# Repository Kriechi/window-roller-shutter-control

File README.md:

# Window Roller Shutter Control 3-gang with ESP8266

This project contains a 3-gang electric/motorized window roller shutter control
based on an ESP8266. The following resources are included:

* Full schematics and PCB designs
  * in KiCAD 5 with all footprints
  * generated Gerber files ready to send to PCB manufacturer
  * exported as PDF file
* Microcontroller ESP8266 firmware source code
  * with WiFi connectivity and remote over-the-air update
  * for control via MQTT and a web interface
* 3D-printable enclosure
  * in 3MF and STL file formats

## Hardware

This projects was designed to control 3 independent electric roller shutter
motors, each with a hot (live) and two switched directional wires (L1 for "up"
and L2 for "down"). Existing manual switches need to be removed and the motor
cables are wired to screw terminals on the PCB. Two relays per roller shutter
control the direction: up or down. The circuit and the relay type ensure that
only one direction is possible at a time. The relays open before closing
(break-before-make), and both relays are arranged "in series" to control the
motor direction.

The PCB and enclosure are designed to fit around an existing 3-gang 60mm switch
box. Any common 3-gang switch plate for this size can be replaced by the PCB and
enclosure, given that each switch box is 72mm apart from its neighbor switch
box. The enclosure mounts flush against the wall and is secured by multiple
screws into the switch box behind it.

Since not every roller shutter provides a neutral (return) wire, an external
5-24VDC power supply (wall plug) is used to power the ESP8266 and relays on PCB.
This securely separates low-voltage from high-voltage, also see separation slots
on the PCB. Multiple footprints are on the PCB to feed in DC low-voltage.

Momentary toggle switches can be added to manually control the roller shutters,
independent of the ESP8266 or automation. The enclosure is designed for 6mm
toggle switches. They control the relays low-voltage side and override signals
from the ESP8266.

### Bill of Material

For the PCB assembly:

* 1x NodeMCU module for ESP8266, or ESP-12E module (requires additional components)
* 3x HB-9500 3P screw terminal, 9.5mm pitch
* 6x SRD-05VDC-SL-C relay, 5VDC control, opening before closing, 10A@250VAC
* 6x NPN transistor, footprint SOT-23, 2N3904 or similar
* 6x 220 Ohm resistor, footprint 1206
* 6x flyback diode, footprint 1206, 1N4001 or similar
* 3x MTS-123 On-Off-On toggle switch
* 1x 5V DC-DC voltage regulator, footprint SOT-223-3, AMS1117-50 or similar
* 1x 3.3V DC-DC voltage regulator if ESP-12E is used, footprint SOT-223-3, AMS1117-33 or similar
* 1x suitable power supply for 5VDC, at least 10W
* optional: capacitors as needed per voltage rail

For the enclosure and mounting:

* 8x M3 nut
* 4x M3x12 bolts
* 2x 3.2mm switch box screws (optional, up to 6x)

### Wiring

Each roller shutter is controlled by two relays accessible via a 3-way screw
terminal block. The center connection is the hot / live wire. The outer
connections are the directional L1 and L2 wires. If you roller shutters is
moving in the wrong direction, e.g., up instead of down, simply reverse the
wires on the outer connections on the this screw terminal block.

The toggle switches are wired in a similar way: the center pin is the common
connection, and the two outer pins control the up or down signal to the ESP8266.

The ESP8266 ESP-12E module needs an external 3.3V regulator, while the NodeMCU
module has one built in and only needs a 5V input (see available footprints on
the PCB). Various footprints for decoupling capacitors are available and can be
populated.

## Firmware / Control Software

The ESP8266 microcontroller can be flashed with the provided PlatformIO-based
firmware project. It controls the following functions:

* WiFi connectivity
* MQTT connection
  * with status updates being published to `window_shutter_status` topic
  * with action commands being subscribed to on the `window_shutter` topic
* Web interface
  * to invoke commands via a browser-based UI
  * similar actions as via MQTT
* Over-the-air updates

All credentials and configuration is placed in `include/credentials.h`, see the
included template file for structure and variable names: WiFi SSID and
passphrase; MQTT server, username and password; and optional an OTA password.

After power-up and connecting to a WiFi network, the web-based UI is available
on the assigned IP address via HTTP (port 80). It is a simple frontend for the
following HTTP calls:

* `/action?q=...` with `...` being an action or preset
  * `1u` or `1up` to move the first shutter up
  * `1d` or `1down` to move the first shutter down
  * `2u` or `2up` to move the second shutter up
  * `2d` or `2down` to move the second shutter down
  * `3u` or `3up` to move the third shutter up
  * `3d` or `3down` to move the third shutter down
  * `preset_work`, `preset_normal`, `preset_night` activates one of the hardcoded presets
  * `s` or `stop` is the same as `/stop`
* `/stop` to stop all roller shutters by disabling the relays
* `/restart` to restart the ESP8266 microcontroller

Similar to the web UI, an MQTT connection is established after power-up and two
topics are use:

* status updates are published to `window_shutter_status`
  * contains state change messages and debug information
* commands can be published to `window_shutter` for the ESP8266 to act upon with a payload
  * `1u` or `1up` to move the first shutter up
  * `1d` or `1down` to move the first shutter down
  * `2u` or `2up` to move the second shutter up
  * `2d` or `2down` to move the second shutter down
  * `3u` or `3up` to move the third shutter up
  * `3d` or `3down` to move the third shutter down
  * `preset_work`, `preset_normal`, `preset_night` activates one of the hardcoded presets
  * `s` or `stop` to stop all roller shutters by disabling the relays
  * `restart` to restart the ESP8266 microcontroller

See [PlatformIO](https://platformio.org/) for more information on how to get
started, compile, and upload the firmware.

Quick development commands:

* compile and verify the code: `platformio run`
* compile and upload the code: `platformio run --target upload`
* get a serial console of the device: `platformio device monitor`

## Caveats

During power-up of the ESP8266, some pins might change state and trigger a relay
to close, before the firmware sets the correct state. This momentary change can
activate the roller shutter for a fraction of a second but is not happening
during normal operation.

If the used power supply is not capable of providing enough switching current
when the relays activate, you can bump up the input voltage to 7.5 or 9VDC, or
add more capacitance on the regulated 5VDC rail.

The toggle switches directly activate the relay, bypassing the
ESP8266-controlled transistors. However, due to the "in series" arrangement of
both relays, if the ESP8266 sends a "down" signal, a toggle switch might not be
able to override it in one direction.

When using an ESP-12E module, extra pull-up or pull-down resistors might be
needed (no footprints on the PCB). The NodeMCU module can be inserted into
standard 2.54mm headers and works with only a 5VDC input voltage.

## License

This project is made available under the MIT License. For more details, see the
``LICENSE`` file in the repository.

## Author

This project was created by Thomas Kriechbaumer.

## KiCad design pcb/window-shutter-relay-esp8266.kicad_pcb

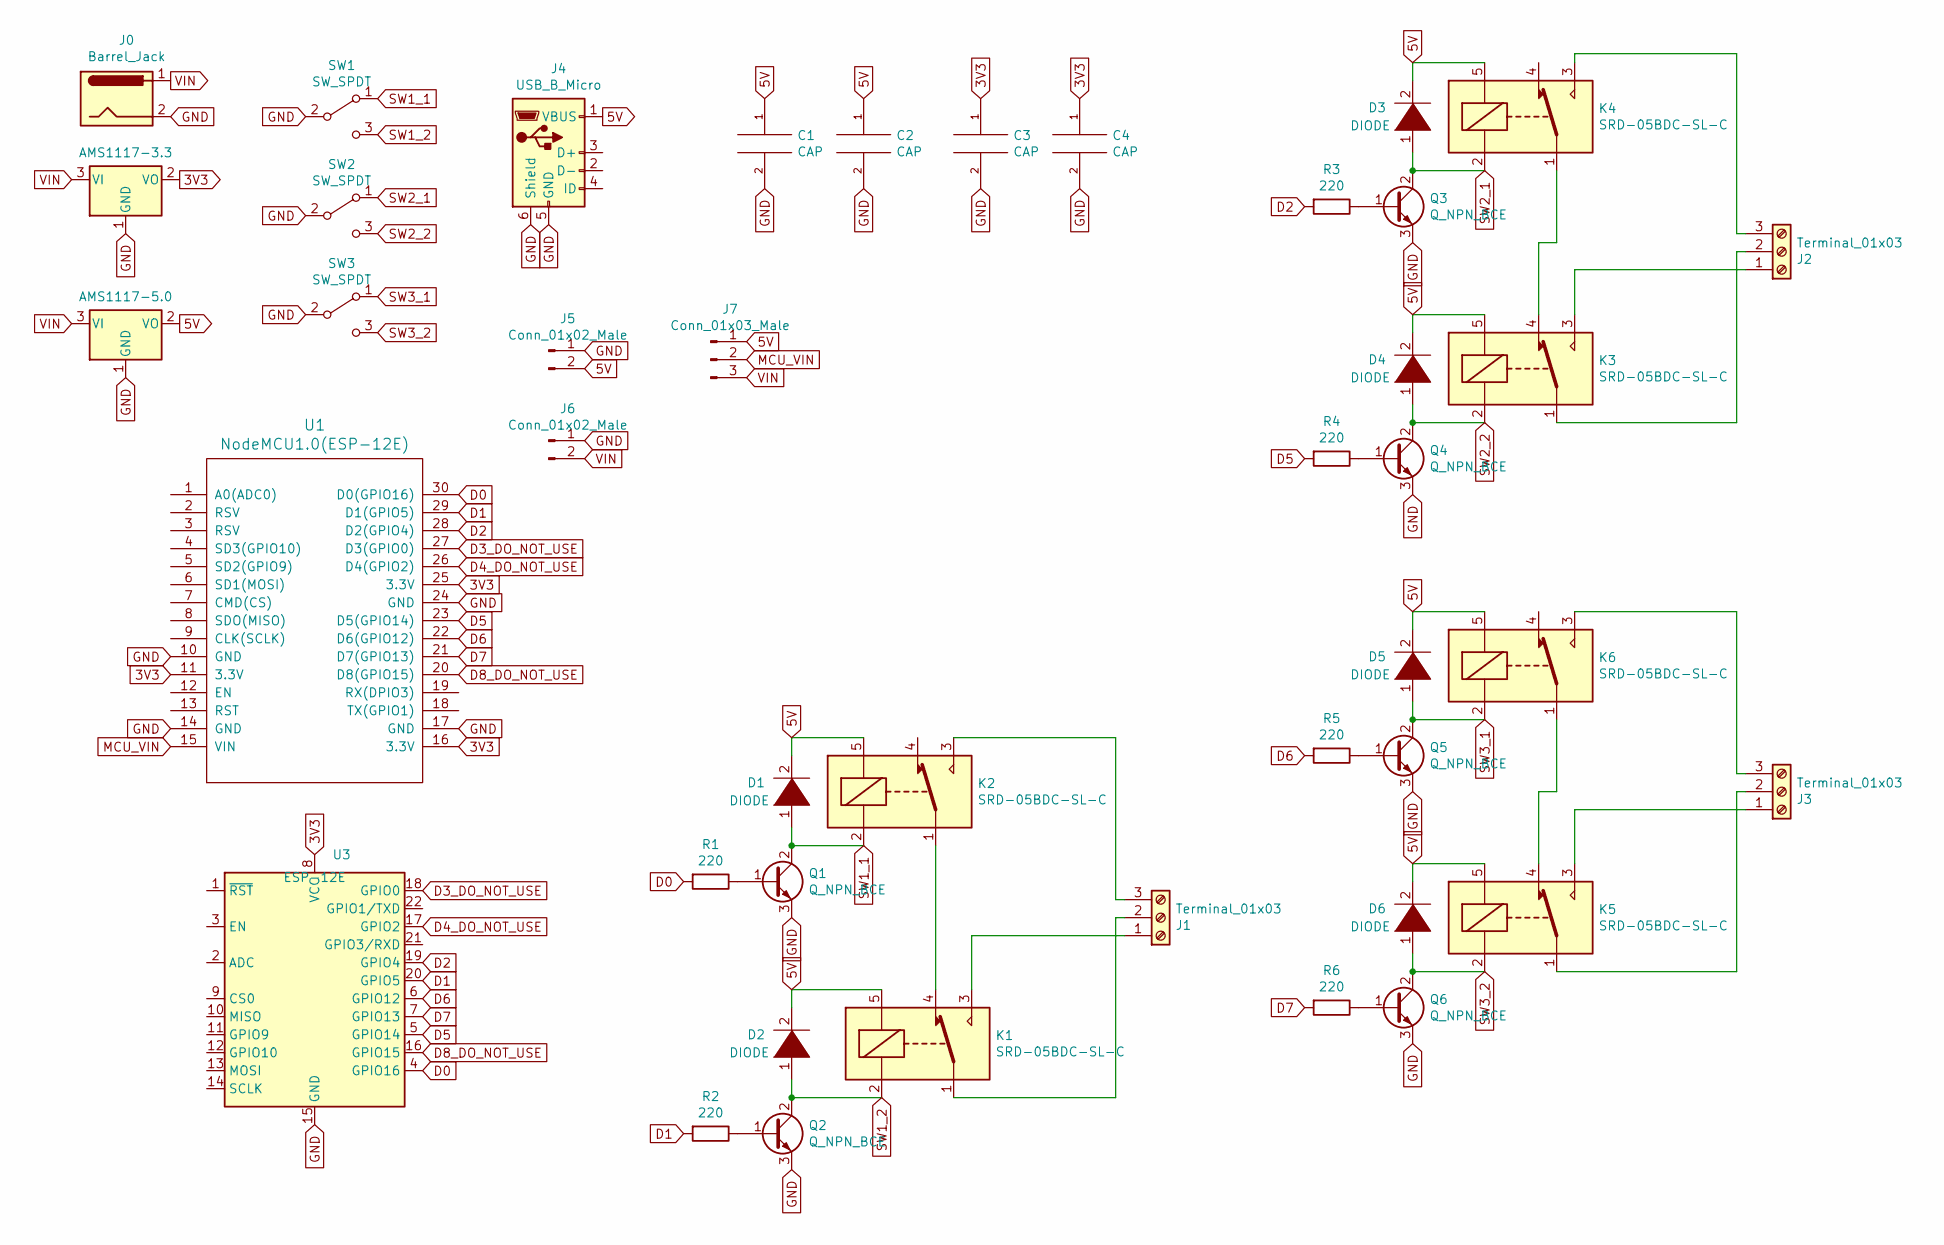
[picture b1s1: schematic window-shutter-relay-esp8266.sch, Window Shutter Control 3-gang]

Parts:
C1, C2, C3, C4: CAP; CP_Radial_D4.0mm_P2.00mm
D1, D2, D3, D4, D5, D6: DIODE; LED_1206_HandSoldering
J0: Barrel_Jack; Barrel_Jack_CUI_PJ-036AH-SMT
J1, J2, J3: Terminal_01x03; TerminalBlock_HB-9500-3_P9.50mm
J4: USB_B_Micro; USB_Micro-B
J5, J6: Conn_01x02_Male; Pin_Header_Straight_1x02_Pitch2.54mm
J7: Conn_01x03_Male; Pin_Header_Straight_1x03_Pitch2.54mm
K1, K2, K3, K4, K5, K6: SRD-05BDC-SL-C; Relay_SPDT_SANYOU_SRD_Series_Form_C
Q1, Q2, Q3, Q4, Q5, Q6: Q_NPN_BCE; SOT-23_Handsoldering
R1, R2, R3, R4, R5, R6: 220; R_1206_HandSoldering
SW1, SW2, SW3: SW_SPDT; Pin_Header_Straight_1x03_Pitch2.54mm
U1: NodeMCU1.0(ESP-12E); NodeMCU-LoLinV3
U2: AMS1117-5.0; SOT-223-3_TabPin2
U3: ESP-12E; ESP-12E_SMD
U4: AMS1117-3.3; SOT-223-3_TabPin2

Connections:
3V3: C3.1, C4.1, U1.11 (3.3V), U1.16 (3.3V), U1.25 (3.3V), U3.8 (VCC), U4.2 (VO)
5V: C1.1, C2.1, D1.2 (A), D2.2 (A), D3.2 (A), D4.2 (A), D5.2 (A), D6.2 (A), J4.1 (VBUS), J5.2, J7.1, K1.5, K2.5, K3.5, K4.5, K5.5, K6.5, U2.2 (VO)
D0: R1.2, U1.30 (D0(GPIO16)), U3.4 (GPIO16)
D1: R2.2, U1.29 (D1(GPIO5)), U3.20 (GPIO5)
D2: R3.2, U1.28 (D2(GPIO4)), U3.19 (GPIO4)
D3_DO_NOT_USE: U1.27 (D3(GPIO0)), U3.18 (GPIO0)
D4_DO_NOT_USE: U1.26 (D4(GPIO2)), U3.17 (GPIO2)
D5: R4.2, U1.23 (D5(GPIO14)), U3.5 (GPIO14)
D6: R5.2, U1.22 (D6(GPIO12)), U3.6 (GPIO12)
D7: R6.2, U1.21 (D7(GPIO13)), U3.7 (GPIO13)
D8_DO_NOT_USE: U1.20 (D8(GPIO15)), U3.16 (GPIO15)
GND: C1.2, C2.2, C3.2, C4.2, J0.2, J4.5 (GND), J4.6 (Shield), J5.1, J6.1, Q1.3 (E), Q2.3 (E), Q3.3 (E), Q4.3 (E), Q5.3 (E), Q6.3 (E), SW1.2 (B), SW2.2 (B), SW3.2 (B), U1.10 (GND), U1.14 (GND), U1.17 (GND), U1.24 (GND), U2.1 (GND), U3.15 (GND), U4.1 (GND)
MCU_VIN: J7.2, U1.15 (VIN)
unnamed: J1.1, K1.3
unnamed: J1.2, K1.1
unnamed: J1.3, K2.3
unnamed: J2.1, K3.3
unnamed: J2.2, K3.1
unnamed: J2.3, K4.3
unnamed: J3.1, K5.3
unnamed: J3.2, K5.1
unnamed: J3.3, K6.3
unnamed: K1.4, K2.1
unnamed: K3.4, K4.1
unnamed: K5.4, K6.1
unnamed: Q1.1 (B), R1.1
unnamed: Q2.1 (B), R2.1
unnamed: Q3.1 (B), R3.1
unnamed: Q4.1 (B), R4.1
unnamed: Q5.1 (B), R5.1
unnamed: Q6.1 (B), R6.1
SW1_1: D1.1 (K), K2.2, Q1.2 (C), SW1.1 (A)
SW1_2: D2.1 (K), K1.2, Q2.2 (C), SW1.3 (C)
SW2_1: D3.1 (K), K4.2, Q3.2 (C), SW2.1 (A)
SW2_2: D4.1 (K), K3.2, Q4.2 (C), SW2.3 (C)
SW3_1: D5.1 (K), K6.2, Q5.2 (C), SW3.1 (A)
SW3_2: D6.1 (K), K5.2, Q6.2 (C), SW3.3 (C)
VIN: J0.1, J6.2, J7.3, U2.3 (VI), U4.3 (VI)

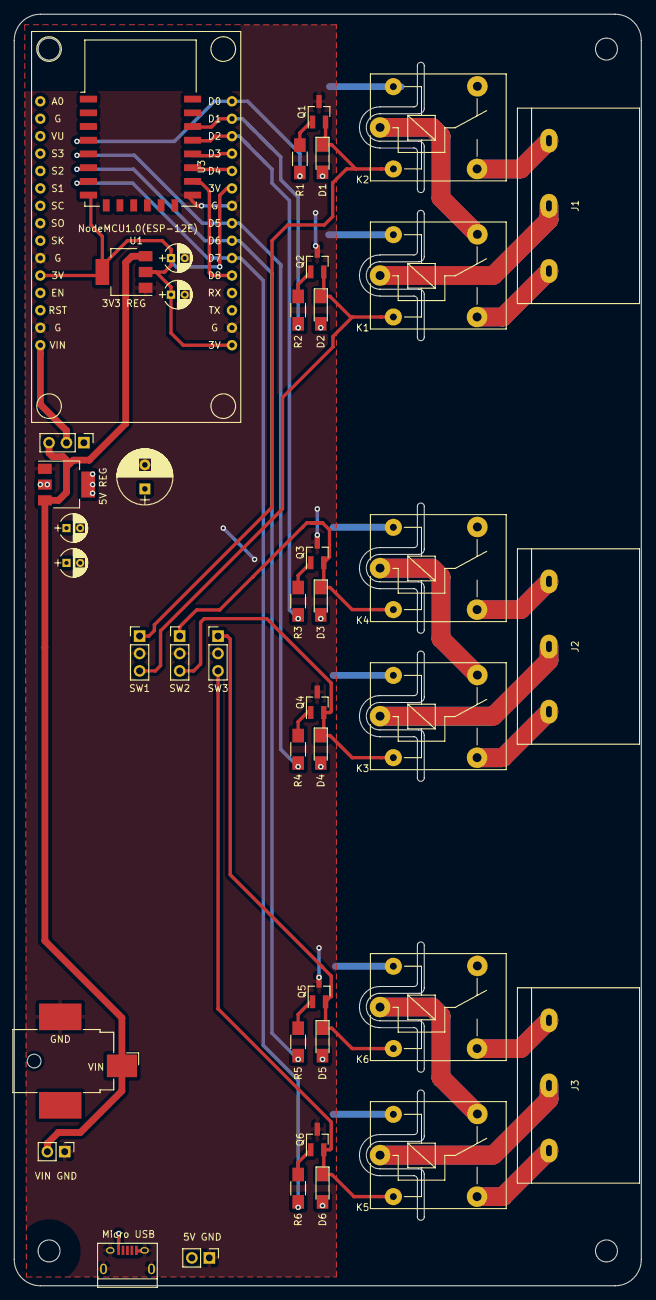
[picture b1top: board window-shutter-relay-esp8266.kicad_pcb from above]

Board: 2 copper layers, 91.4 x 185.4 mm, 43 parts (0 on the bottom side), 38 nets.

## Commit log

2021-11-29 minor changes
    add aggressive caching, Apple app tag, change text size
2022-01-29 add global disable/enable switch for all shutter actions
2022-11-20 KiCAD upgrade
2022-11-20 use secure TLS MQTT connection
2022-11-20 improve preset enable
